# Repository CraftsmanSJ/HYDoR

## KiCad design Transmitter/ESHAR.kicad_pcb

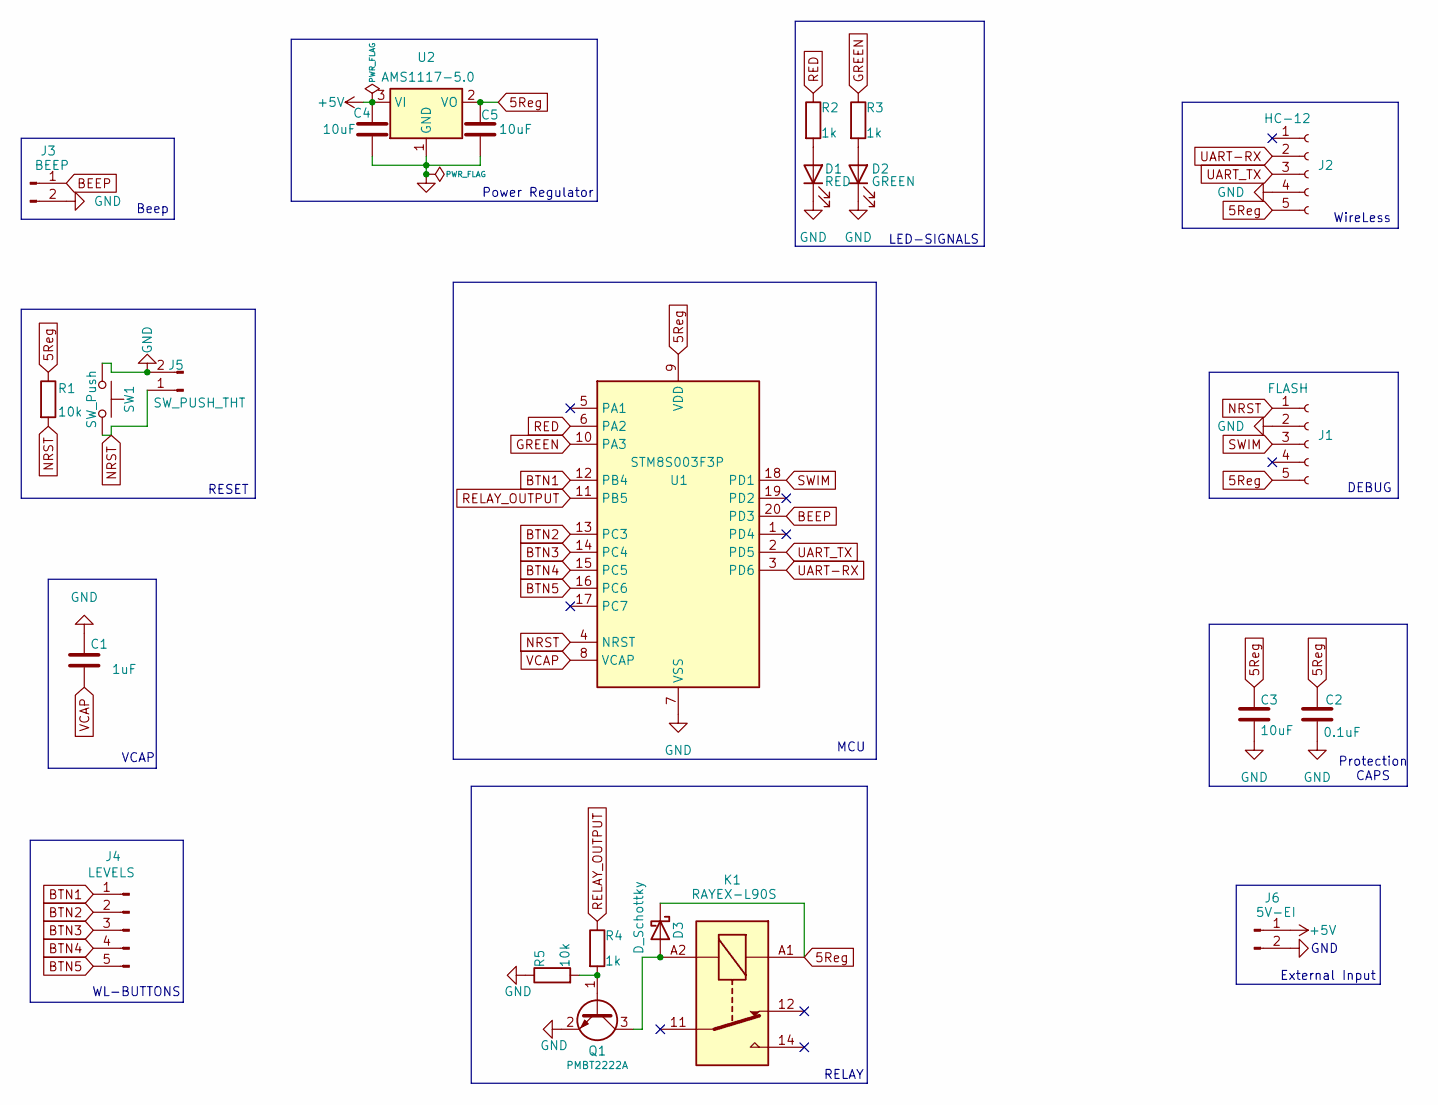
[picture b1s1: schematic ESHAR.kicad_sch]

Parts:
C1: 1uF; C_0805_2012Metric
C2: 0.1uF; C_0805_2012Metric
C3, C4, C5: 10uF; C_0805_2012Metric
D1: RED; LED_D5.0mm
D2: GREEN; LED_D5.0mm
D3: D_Schottky; D_SMA
J1: FLASH; PinHeader_1x05_P1.00mm_Vertical
J2: HC-12; PinSocket_1x05_P2.00mm_Vertical
J3: BEEP; PinHeader_1x02_P1.00mm_Vertical
J4: LEVELS; PinHeader_1x05_P1.00mm_Vertical
J5: SW_PUSH_THT; PinHeader_1x02_P1.00mm_Vertical
J6: 5V-EI; PinHeader_1x02_P1.00mm_Vertical
K1: RAYEX-L90S; Relay_SPDT_RAYEX-L90S
Q1: PMBT2222A; SOT-23
R1, R5: 10k; R_0805_2012Metric
R2, R3, R4: 1k; R_0805_2012Metric
SW1: SW_Push; SW_PUSH_6mm
U1: STM8S003F3P; TSSOP-20_4.4x6.5mm_P0.65mm
U2: AMS1117-5.0; SOT-223-3_TabPin2

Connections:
5Reg: C2.1, C3.1, C5.1, D3.1 (K), J1.5, J2.5, K1.A1, R1.1, U1.9 (VDD), U2.2 (VO)
+5V: C4.1, J6.1, U2.3 (VI)
BEEP: J3.1, U1.20 (PD3)
BTN1: J4.1, U1.12 (PB4)
BTN2: J4.2, U1.13 (PC3)
BTN3: J4.3, U1.14 (PC4)
BTN4: J4.4, U1.15 (PC5)
BTN5: J4.5, U1.16 (PC6)
GND: C1.1, C2.2, C3.2, C4.2, C5.2, D1.1 (K), D2.1 (K), J1.2, J2.4, J3.2, J5.2, J6.2, Q1.2 (E), R5.1, SW1.1, U1.7 (VSS), U2.1 (GND)
GREEN: R3.1, U1.10 (PA3)
NRST: J1.1, J5.1, R1.2, SW1.2, U1.4 (NRST)
unnamed: D1.2 (A), R2.2
unnamed: D2.2 (A), R3.2
unnamed: D3.2 (A), K1.A2, Q1.3 (C)
unnamed: Q1.1 (B), R4.2, R5.2
RED: R2.1, U1.6 (PA2)
RELAY_OUTPUT: R4.1, U1.11 (PB5)
SWIM: J1.3, U1.18 (PD1)
UART-RX: J2.2, U1.3 (PD6)
UART_TX: J2.3, U1.2 (PD5)
VCAP: C1.2, U1.8 (VCAP)

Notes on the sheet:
Protection CAPS
WireLess
External Input
VCAP
MCU
WL-BUTTONS
Power Regulator
LED-SIGNALS
GND
Beep
DEBUG
RELAY
RESET

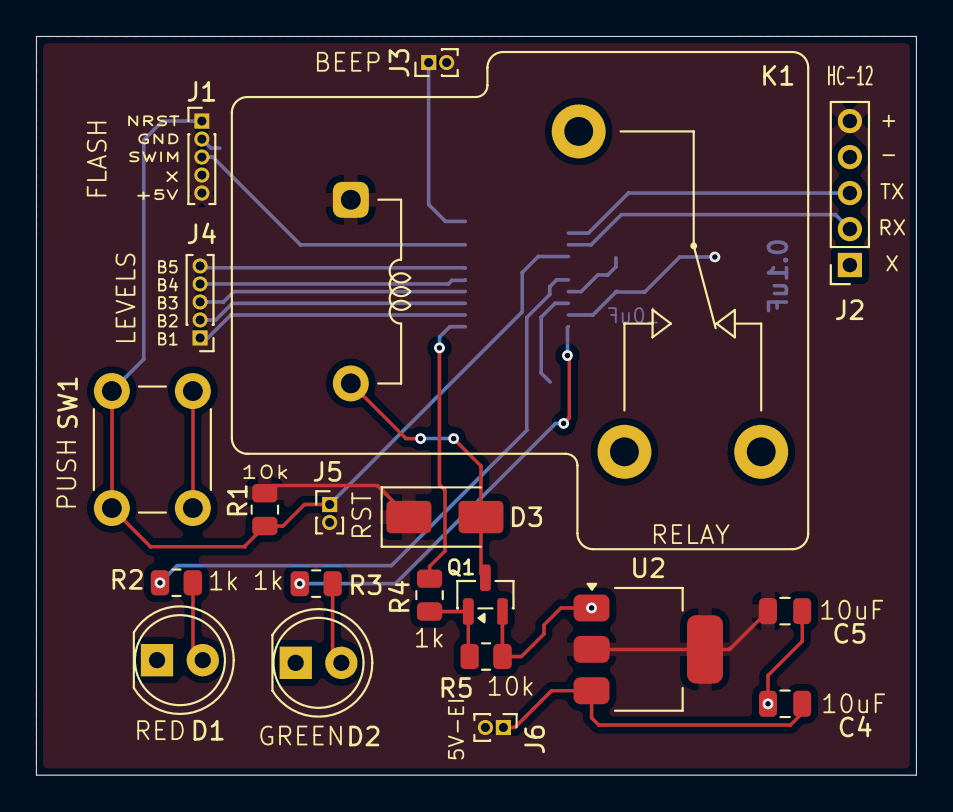
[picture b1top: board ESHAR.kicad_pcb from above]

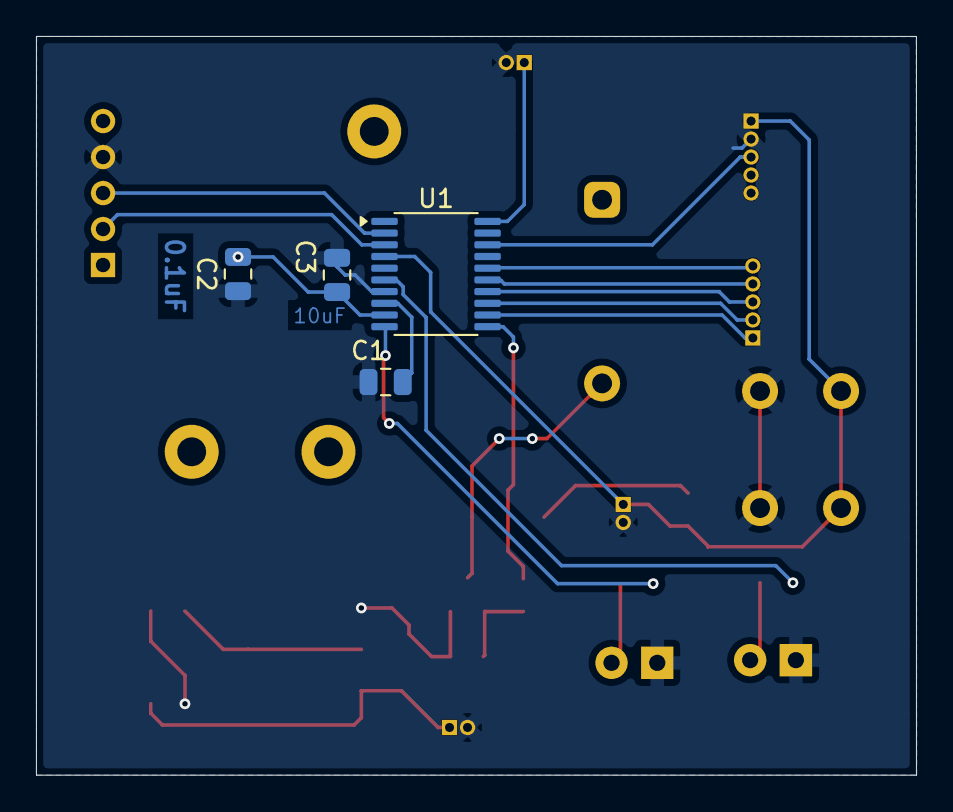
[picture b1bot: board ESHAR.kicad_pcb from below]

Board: 2 copper layers, 48.9 x 41.0 mm, 24 parts (4 on the bottom side), 21 nets.
